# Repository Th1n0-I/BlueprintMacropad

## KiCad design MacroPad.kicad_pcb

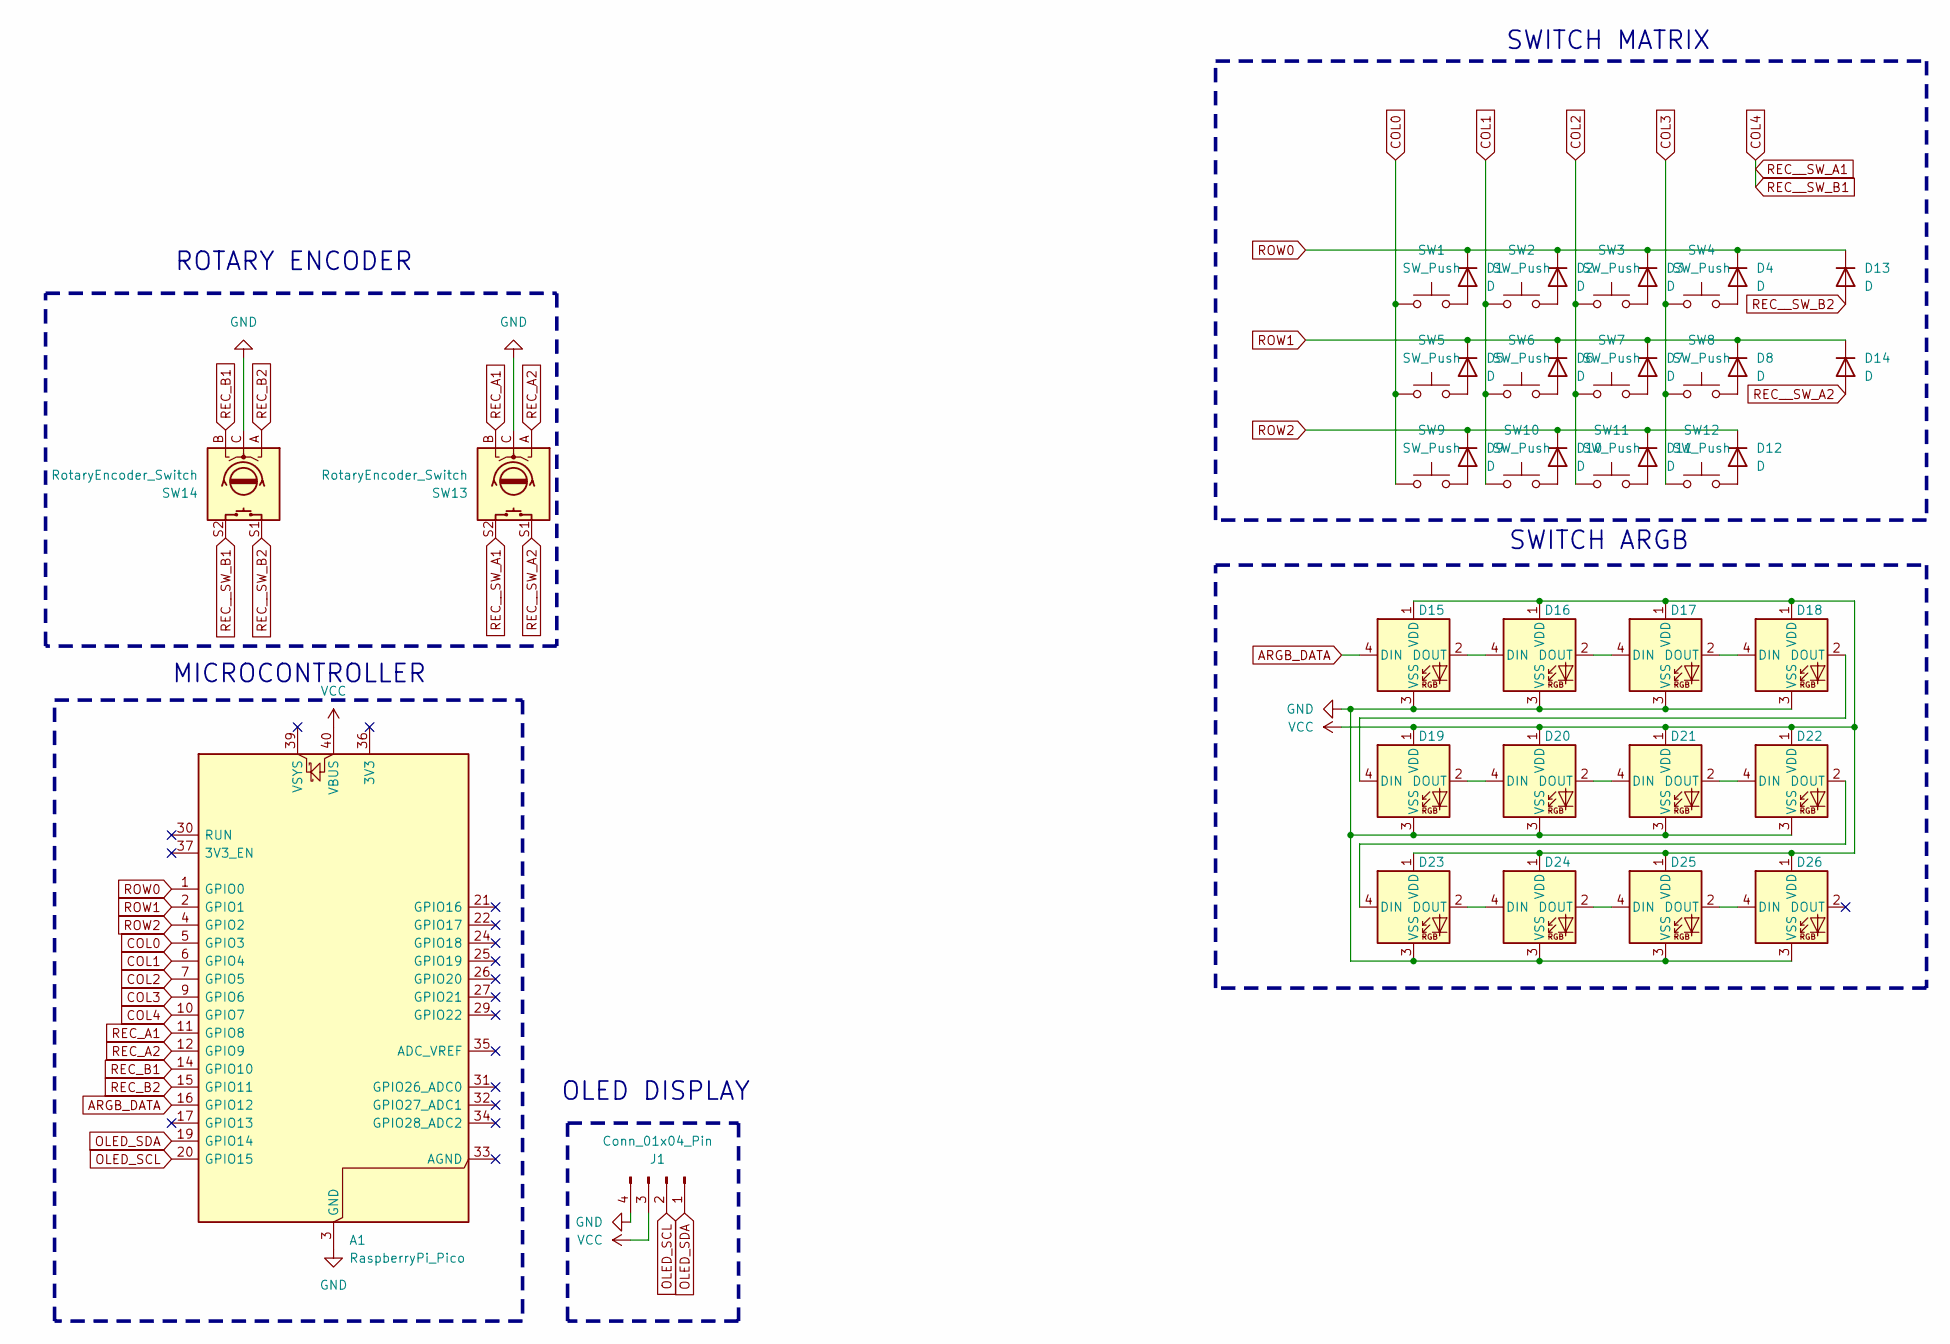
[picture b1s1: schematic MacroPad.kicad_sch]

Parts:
A1: RaspberryPi_Pico; RaspberryPi_Pico_Common_Unspecified
D1, D2, D3, D4, D5, D6, D7, D8, D9, D10, D11, D12, D13, D14: D; D_DO-35_SOD27_P7.62mm_Horizontal
D15, D16, D17, D18, D19, D20, D21, D22, D23, D24, D25, D26: SK6812MINI-E; SK6812MINI-E_fixed
J1: Conn_01x04_Pin; PinHeader_1x04_P2.54mm_Vertical
SW1, SW2, SW3, SW4, SW5, SW6, SW7, SW8, SW9, SW10, SW11, SW12: SW_Push; SW_Cherry_MX_1.00u_PCB
SW13, SW14: RotaryEncoder_Switch; RotaryEncoder_Alps_EC11E-Switch_Vertical_H20mm

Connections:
ARGB_DATA: A1.16 (GPIO12), D15.4 (DIN)
COL0: A1.5 (GPIO3), SW1.1, SW5.1, SW9.1
COL1: A1.6 (GPIO4), SW2.1, SW6.1, SW10.1
COL2: A1.7 (GPIO5), SW3.1, SW7.1, SW11.1
COL3: A1.9 (GPIO6), SW4.1, SW8.1, SW12.1
COL4: A1.10 (GPIO7), SW13.S2, SW14.S2
GND: A1.3 (GND), A1.8 (GND), A1.13 (GND), A1.18 (GND), A1.23 (GND), A1.28 (GND), A1.38 (GND), D15.3 (VSS), D16.3 (VSS), D17.3 (VSS), D18.3 (VSS), D19.3 (VSS), D20.3 (VSS), D21.3 (VSS), D22.3 (VSS), D23.3 (VSS), D24.3 (VSS), D25.3 (VSS), D26.3 (VSS), J1.4, SW13.C, SW14.C
unnamed: D1.2 (A), SW1.2
unnamed: D2.2 (A), SW2.2
unnamed: D3.2 (A), SW3.2
unnamed: D4.2 (A), SW4.2
unnamed: D5.2 (A), SW5.2
unnamed: D6.2 (A), SW6.2
unnamed: D7.2 (A), SW7.2
unnamed: D8.2 (A), SW8.2
unnamed: D9.2 (A), SW9.2
unnamed: D10.2 (A), SW10.2
unnamed: D11.2 (A), SW11.2
unnamed: D12.2 (A), SW12.2
unnamed: D15.2 (DOUT), D16.4 (DIN)
unnamed: D16.2 (DOUT), D17.4 (DIN)
unnamed: D17.2 (DOUT), D18.4 (DIN)
unnamed: D18.2 (DOUT), D19.4 (DIN)
unnamed: D19.2 (DOUT), D20.4 (DIN)
unnamed: D20.2 (DOUT), D21.4 (DIN)
unnamed: D21.2 (DOUT), D22.4 (DIN)
unnamed: D22.2 (DOUT), D23.4 (DIN)
unnamed: D23.2 (DOUT), D24.4 (DIN)
unnamed: D24.2 (DOUT), D25.4 (DIN)
unnamed: D25.2 (DOUT), D26.4 (DIN)
OLED_SCL: A1.20 (GPIO15), J1.2
OLED_SDA: A1.19 (GPIO14), J1.1
REC_A1: A1.11 (GPIO8), SW13.B
REC_A2: A1.12 (GPIO9), SW13.A
REC_B1: A1.14 (GPIO10), SW14.B
REC_B2: A1.15 (GPIO11), SW14.A
REC__SW_A2: D14.2 (A), SW13.S1
REC__SW_B2: D13.2 (A), SW14.S1
ROW0: A1.1 (GPIO0), D1.1 (K), D2.1 (K), D3.1 (K), D4.1 (K), D13.1 (K)
ROW1: A1.2 (GPIO1), D5.1 (K), D6.1 (K), D7.1 (K), D8.1 (K), D14.1 (K)
ROW2: A1.4 (GPIO2), D9.1 (K), D10.1 (K), D11.1 (K), D12.1 (K)
VCC: A1.40 (VBUS), D15.1 (VDD), D16.1 (VDD), D17.1 (VDD), D18.1 (VDD), D19.1 (VDD), D20.1 (VDD), D21.1 (VDD), D22.1 (VDD), D23.1 (VDD), D24.1 (VDD), D25.1 (VDD), D26.1 (VDD), J1.3

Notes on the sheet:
MICROCONTROLLER
OLED DISPLAY
SWITCH MATRIX
SWITCH ARGB
ROTARY ENCODER

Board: 2 copper layers, 42 parts (26 on the bottom side), 42 nets, no tracks yet.

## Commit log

2026-02-18 Feat: Initial commit
2026-02-18 Feat: Complete schematic and started pcb
2026-02-19 Feat: Designed the PCB
2026-02-22 feat: more design
2026-02-22 feat: switched switches
2026-02-25 feat: change blueprints
